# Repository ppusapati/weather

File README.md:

# Weather Station Firmware

## STM32F407 Weather Station — Embedded Rust Firmware

A production-grade weather station firmware written in Rust targeting the **STM32F407VGT6** MCU.
It collects environmental data from multiple sensors and transmits readings over
**WiFi (ATWINC1500), BLE (RN4870), LoRa, UART, MQTT, and HTTP** — with optional
Ethernet (W5500) and Cellular (SIM7600E-H) connectivity.

---

## Architecture Overview

```
┌─────────────────────────────────────────────────────────────┐
│                    APPLICATION LAYER                        │
│  ┌──────────┐ ┌────────────┐ ┌──────────┐ ┌────────────┐  │
│  │Scheduler │ │Data Pipeline│ │  Power   │ │    OTA     │  │
│  │          │ │  & Fusion  │ │  Mgmt    │ │  Updater   │  │
│  └──────────┘ └────────────┘ └──────────┘ └────────────┘  │
├─────────────────────────────────────────────────────────────┤
│                  COMMUNICATION LAYER                        │
│  ┌──────┐ ┌─────┐ ┌──────┐ ┌──────┐ ┌──────┐ ┌────────┐  │
│  │ WiFi │ │ BLE │ │ LoRa │ │ UART │ │ MQTT │ │  HTTP  │  │
│  └──────┘ └─────┘ └──────┘ └──────┘ └──────┘ └────────┘  │
├─────────────────────────────────────────────────────────────┤
│                     DRIVER LAYER                            │
│  ┌───────┐ ┌──────────┐ ┌──────┐ ┌──────┐ ┌───────────┐  │
│  │BME280 │ │Wind Speed│ │ Rain │ │  UV  │ │   Light   │  │
│  │Temp/  │ │& Dir     │ │Gauge │ │Index │ │  (BH1750) │  │
│  │Hum/Pr │ │(AS5600)  │ │(Tip) │ │SI1145│ │           │  │
│  └───────┘ └──────────┘ └──────┘ └──────┘ └───────────┘  │
├─────────────────────────────────────────────────────────────┤
│                 HARDWARE ABSTRACTION                        │
│  ┌──────┐ ┌──────┐ ┌──────┐ ┌──────┐ ┌──────┐ ┌───────┐  │
│  │ I2C  │ │ SPI  │ │ ADC  │ │ GPIO │ │ UART │ │ Timer │  │
│  └──────┘ └──────┘ └──────┘ └──────┘ └──────┘ └───────┘  │
├─────────────────────────────────────────────────────────────┤
│                   STM32F407 HARDWARE                        │
│  ARM Cortex-M4F @ 168 MHz · 192KB SRAM · 1MB Flash        │
└─────────────────────────────────────────────────────────────┘
```

## MCU Selection — STM32F407VGT6

| Criterion | STM32F407VGT6 |
|---|---|
| CPU | ARM Cortex-M4F @ 168 MHz (with FPU) |
| RAM | 192 KB SRAM (128 KB + 64 KB CCM) |
| Flash | 1 MB internal |
| WiFi | ATWINC1500 module (SPI3) |
| Bluetooth | RN4870 BLE 5.0 module (USART3) |
| ADC | 3x 12-bit SAR, 16 channels |
| I2C / SPI / UART | 3 / 3 / 4 |
| GPIO | 82 programmable |
| Standby | ~2 µA |
| Temp range | -40°C to +105°C (Industrial) |
| Rust support | `stm32f4xx-hal` + `cortex-m-rt` (mature) |

**Why STM32F407?** Industrial temperature range for outdoor deployment, hardware FPU for
sensor math, three SPI buses for concurrent LoRa/Ethernet/WiFi, dedicated UART for each
communication module, and excellent Rust embedded-hal support. Single-MCU architecture
simplifies firmware (one codebase, one toolchain).

## Sensors

| Sensor | Measures | Interface | Address / Pin |
|---|---|---|---|
| BME280 | Temperature, humidity, pressure | I2C | 0x76 |
| AS5600 | Wind direction (magnetic encoder) | I2C | 0x36 |
| Anemometer | Wind speed (pulse count) | GPIO interrupt | GPIO 4 |
| Rain gauge | Rainfall (tipping bucket) | GPIO interrupt | GPIO 5 |
| SI1145 | UV index | I2C | 0x60 |
| BH1750 | Ambient light (lux) | I2C | 0x23 |

## Communication Channels

| Channel | Protocol | Use Case |
|---|---|---|
| **WiFi** | 802.11n | Primary uplink to cloud/MQTT broker |
| **BLE 5.0** | GATT | Mobile app config & live readings |
| **LoRa** | LoRaWAN (SX1276 via SPI) | Long-range low-power telemetry |
| **UART** | Serial 115200 | Debug console & wired data export |
| **MQTT** | MQTT v3.1.1 over TCP/TLS | Cloud telemetry (over WiFi) |
| **HTTP** | REST JSON API | Local web dashboard + OTA updates |

## Industry Modules

The firmware supports optional industry-specific extensions via Cargo features:

| Feature | Industry | Additional Sensors | Analytics |
|---------|----------|-------------------|-----------|
| `agriculture` | Precision Farming | Soil moisture (×2), soil temp, leaf wetness | ET₀, GDD, frost alerts, irrigation scheduling, disease risk, spray windows |
| `solar` | Photovoltaic Monitoring | Pyranometer, panel temp (×2), power meter | Irradiance, yield estimation, peak sun hours, performance ratio, soiling loss, cloud transients |
| `india` | Indian Regional | PM2.5 particulate sensor | Monsoon tracking, IMD heat wave alerts, cyclone detection, NAQI air quality, IST timezone, IN865 LoRa |
| `all-industries` | All | All above | All above |
| `cellular` | Remote Sites | SIM7600E-H LTE modem | Cellular uplink for remote stations |
| `ethernet` | Industrial | W5500 wired Ethernet | Reliable wired connectivity + Modbus TCP |
| `sdcard` | Data Logging | Micro-SD card (SPI2) | FAT32 CSV logging with daily file rotation, GB-scale storage |
| `all-comms` | All Comms | Cellular + Ethernet + SD card | All communication + storage channels |
| `full-system` | Everything | All sensors + all comms | All analytics + SCADA + Cloud |

### Operating Modes

| Mode | Cloud (MQTT/HTTP) | SCADA (Modbus RS485) | Selection |
|------|:-----------------:|:--------------------:|-----------|
| **Cloud** | Yes | — | DIP 0:0 |
| **SCADA** | Yes | Yes | DIP 0:1 |
| **Hybrid** | Yes | Yes | DIP 1:0 (default) |

```bash
# Build with agriculture module
cargo build --release --features agriculture

# Build with solar module
cargo build --release --features solar

# Build with India regional module
cargo build --release --features india

# Build with all industry modules
cargo build --release --features all-industries

# Build with cellular modem support
cargo build --release --features cellular

# Build with Ethernet support
cargo build --release --features ethernet

# Build with SD card data logging
cargo build --release --features sdcard

# Full system: all industries + all comms
cargo build --release --features full-system
```

See [docs/INDUSTRY_AGRICULTURE.md](docs/INDUSTRY_AGRICULTURE.md),
[docs/INDUSTRY_SOLAR.md](docs/INDUSTRY_SOLAR.md),
[docs/INDUSTRY_INDIA.md](docs/INDUSTRY_INDIA.md), and
[docs/STM32_SCADA.md](docs/STM32_SCADA.md) for detailed documentation.

## Building

```bash
# Install Rust + ARM toolchain
rustup install nightly
rustup target add thumbv7em-none-eabihf
cargo install probe-rs-tools

# Build (base weather station)
cd firmware
cargo build --release --target thumbv7em-none-eabihf

# Flash via SWD (ST-Link V2)
probe-rs run --chip STM32F407VGTx target/thumbv7em-none-eabihf/release/weather-station
```

## Project Structure

```
weather/
├── README.md
├── docs/
│   ├── ARCHITECTURE.md
│   ├── REQUIREMENTS.md
│   ├── API.md
│   ├── HARDWARE.md
│   ├── INDUSTRY_INDIA.md
│   └── diagrams/
│       ├── system_architecture.md
│       ├── circuit_diagram.md
│       ├── communication_flow.md
│       ├── state_machine.md
│       ├── data_pipeline.md
│       └── sequence_diagrams.md
├── firmware/
│   ├── Cargo.toml
│   ├── build.rs
│   ├── .cargo/config.toml
│   ├── memory.x
│   └── src/
│       ├── main.rs
│       ├── config.rs
│       ├── error.rs
│       ├── drivers/
│       │   ├── mod.rs
│       │   ├── bme280.rs
│       │   ├── wind.rs
│       │   ├── rain.rs
│       │   ├── uv.rs
│       │   ├── light.rs
│       │   ├── soil_moisture.rs  (agriculture)
│       │   ├── soil_temp.rs      (agriculture/solar)
│       │   ├── leaf_wetness.rs   (agriculture)
│       │   ├── pyranometer.rs    (solar)
│       │   ├── pm25.rs           (india)
│       │   ├── stm32f407.rs     (MCU HAL + pin map)
│       │   ├── atwinc1500.rs   (WiFi SPI driver)
│       │   └── rn4870.rs       (BLE UART driver)
│       ├── comms/
│       │   ├── mod.rs
│       │   ├── wifi.rs
│       │   ├── ble.rs
│       │   ├── lora.rs
│       │   ├── uart_console.rs
│       │   ├── mqtt.rs
│       │   ├── http.rs
│       │   └── modbus_rtu.rs    (Modbus RS485 slave)
│       ├── core/
│       │   ├── mod.rs
│       │   ├── scheduler.rs
│       │   ├── data_pipeline.rs
│       │   ├── power.rs
│       │   ├── ota.rs
│       │   └── mode_manager.rs  (SCADA/Cloud/Hybrid)
│       ├── industry/
│       │   ├── mod.rs
│       │   ├── agriculture.rs    (agriculture)
│       │   ├── solar.rs          (solar)
│       │   └── india.rs          (india)
│       ├── storage/
│       │   ├── mod.rs
│       │   └── flash.rs
│       └── utils/
│           ├── mod.rs
│           ├── fmt.rs
│           ├── ring_buffer.rs
│           └── crc.rs
└── tests/
    └── integration.rs
```

## License

MIT

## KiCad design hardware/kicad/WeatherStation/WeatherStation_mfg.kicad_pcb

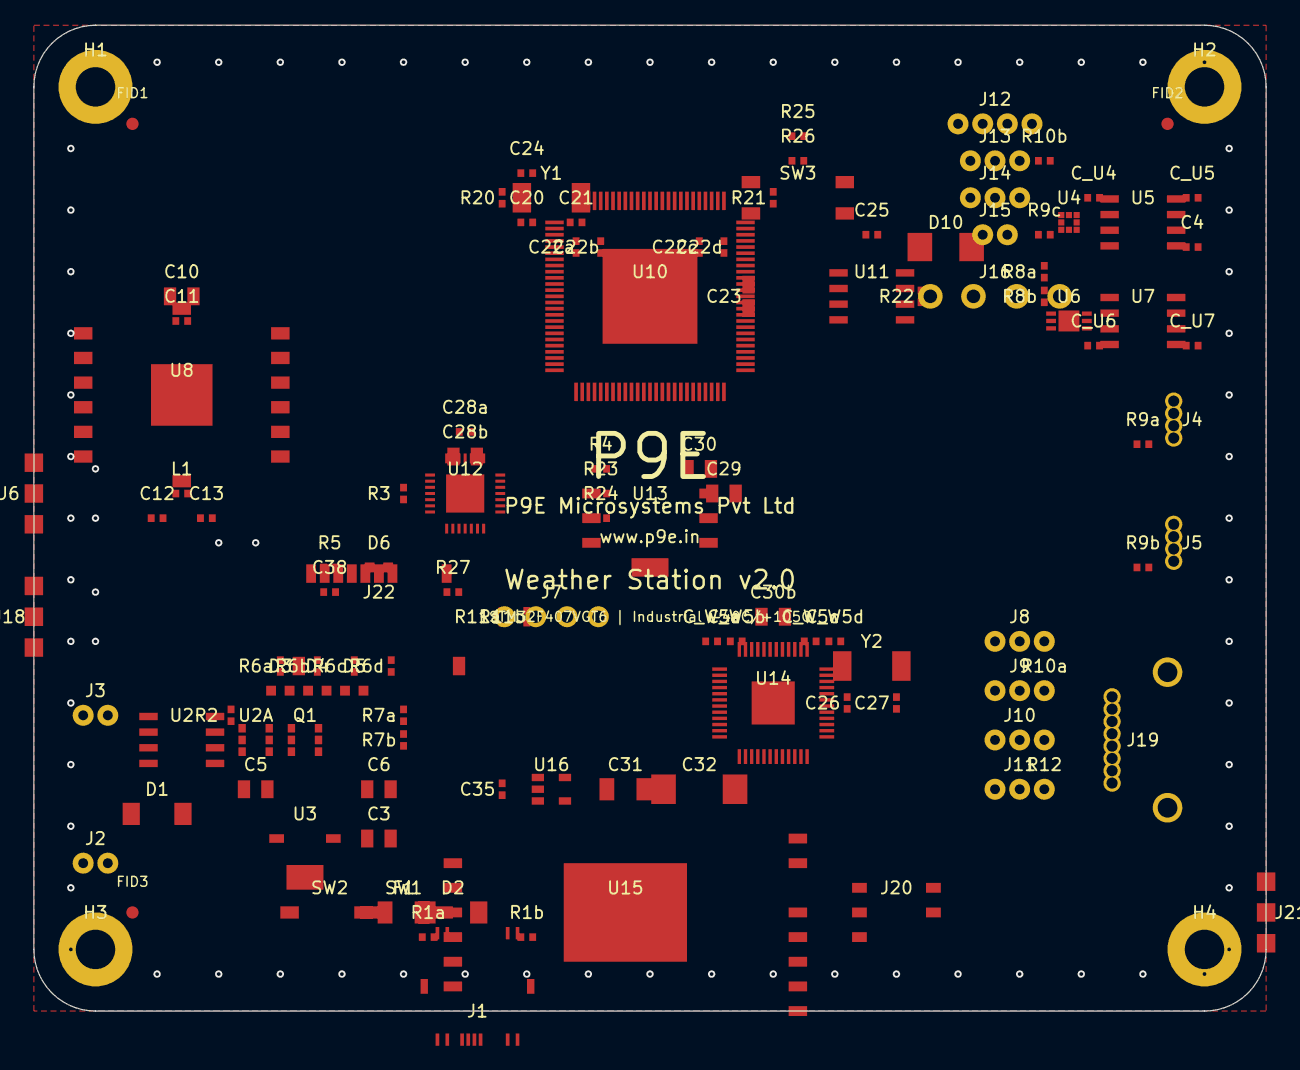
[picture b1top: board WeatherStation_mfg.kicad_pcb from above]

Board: 4 copper layers, 100.0 x 80.0 mm, 124 parts (0 on the bottom side), 76 nets, no tracks yet.

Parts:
C3: 22uF; C_0805_2012Metric
C4, C35: 1uF; C_0402_1005Metric
C5, C6, C10, C28b, C30, C30b: 10uF; C_0805_2012Metric
C11, C22a, C22b, C22c, C22d, C24, C25, C28a, C38: 100nF; C_0402_1005Metric
C12: 1.5pF; C_0402_1005Metric
C13: 3.3pF; C_0402_1005Metric
C20, C21: 20pF; C_0402_1005Metric
C23, C29: 4.7uF; C_0805_2012Metric
C26, C27: 18pF; C_0402_1005Metric
C31: 100uF; C_1206_3216Metric
C32: 470uF; CP_EIA-7343-31_Kemet-D
C_U4, C_U5, C_U6, C_U7: 100nF; C_0402_1005Metric
C_W5a, C_W5b, C_W5c, C_W5d: 100nF; C_0402_1005Metric
D1: SS14; D_SMA
D2: SMAJ5.0A; D_SMA
D3: LED_Red; LED_0603_1608Metric
D4, D6: LED_Green; LED_0603_1608Metric
D5: LED_Blue; LED_0603_1608Metric
D10: SMBJ6.0CA; D_SMB
F1: 500mA; Fuse_1206_3216Metric
FID1, FID2, FID3: Fiducial; Fiducial_1mm_Mask2mm
H1, H2, H3, H4: MountingHole_M3; MountingHole_3.2mm_M3_Pad_Via
J1: USB-C; USB_C_Receptacle_GCT_USB4105
J2: SOLAR_IN; JST_PH_B2B-PH-K_1x02_P2.00mm_Vertical
J3: BATTERY; JST_PH_B2B-PH-K_1x02_P2.00mm_Vertical
J4: ANEMOMETER; RJ11_Amphenol_54601
J5: RAIN_GAUGE; RJ11_Amphenol_54601
J6: SMA_LoRa; SMA_Amphenol_132289_EdgeMount
J7: DEBUG_UART; PinHeader_1x04_P2.54mm_Vertical
J8: SOIL_MOIST_1; JST_PH_B3B-PH-K_1x03_P2.00mm_Vertical
J9: SOIL_MOIST_2; JST_PH_B3B-PH-K_1x03_P2.00mm_Vertical
J10: SOIL_TEMP; JST_PH_B3B-PH-K_1x03_P2.00mm_Vertical
J11: LEAF_WET; JST_PH_B3B-PH-K_1x03_P2.00mm_Vertical
J12: PYRANOMETER; JST_PH_B4B-PH-K_1x04_P2.00mm_Vertical
J13: PANEL_TEMP_F; JST_PH_B3B-PH-K_1x03_P2.00mm_Vertical
J14: PANEL_TEMP_B; JST_PH_B3B-PH-K_1x03_P2.00mm_Vertical
J15: POWER_PULSE; JST_PH_B2B-PH-K_1x02_P2.00mm_Vertical
J16: RS485_Bus; PhoenixContact_MC_01x04_G_3.5mm
J18: SMA_WiFi; SMA_Amphenol_132289_EdgeMount
J19: RJ45_Magjack; RJ45_Amphenol_RJHSE-5380
J20: NanoSIM; NanoSIM_Molex_78800
J21: SMA_LTE; SMA_Amphenol_132289_EdgeMount
J22: MicroSD; MicroSD_Molex_5031821852
L1: 5.6nH; L_0402_1005Metric
Q1: FS8205A; SOT-23-6
R1a, R1b: 5.1k; R_0402_1005Metric
R2: 2.2k; R_0402_1005Metric
R3, R4, R9a, R9b, R9c, R12, R20, R21, R25, R26, R27: 10k; R_0402_1005Metric
R5: 330R; R_0402_1005Metric
R6a, R6b, R6c, R6d: 1k; R_0402_1005Metric
R7a, R7b: 100k; R_0402_1005Metric
R8a, R8b, R10a, R10b: 4.7k; R_0402_1005Metric
R11a, R11b, R23, R24: 100R; R_0402_1005Metric
R22: 120R; R_0402_1005Metric
SW1: BOOT; SW_SPST_PTS645
SW2: RESET; SW_SPST_PTS645
SW3: MODE_DIP; SW_DIP_SPSTx02_Slide_6.7x6.64mm_W8.61mm_P2.54mm
U2: TP4056; SOIC-8_3.9x4.9mm_P1.27mm
U2A: DW01A; SOT-23-6
U3: AMS1117-3.3; SOT-223-3_TabPin2
U4: BME280; Bosch_BME280_LGA-8_2.5x2.5mm
U5: AS5600; SOIC-8_3.9x4.9mm_P1.27mm
U6: SI1145; QFN-10-1EP_3x3mm_P0.6mm
U7: BH1750FVI; SOIC-8_3.9x4.9mm_P1.27mm
U8: SX1276/RFM95W; RFM95W
U10: STM32F407VGT6; LQFP-100_14x14mm_P0.5mm
U11: MAX3485ESA+; SOIC-8_3.9x4.9mm_P1.27mm
U12: ATWINC1500; QFN-28-1EP_5x5mm_P0.5mm_EP3.1x3.1mm
U13: RN4870-I/RM; RN4870_11.5x8mm
U14: W5500; LQFP-48_7x7mm_P0.5mm
U15: SIM7600E-H; SIM7600EH_LCC
U16: TPS7A2033; SOT-23-5
Y1: 8MHz; Crystal_SMD_HC49-SD
Y2: 25MHz; Crystal_SMD_HC49-SD

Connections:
+3V3: C3.1, C4.1, C10.1, C11.1, C22a.1, C22b.1, C22c.1, C22d.1, C23.1, C25.1, C28a.1, C28b.1, C29.1, C30.1, C30b.1, C35.1, C38.1, C_U4.1, C_U5.1, C_U6.1, C_U7.1, C_W5a.1, C_W5b.1, C_W5c.1, C_W5d.1, D5.2, J4.3, J5.3, J7.3, J8.1, J9.1, J10.1, J11.1, J12.1, J13.1, J14.1, J22.4, R3.1, R4.1, R6c.1, R8a.1, R8b.1, R9a.1, R9b.1, R9c.1, R10a.1, R10b.1, R20.1, R27.1, U3.2, U4.5, U4.8, U5.7, U5.8, U6.6, U7.1, U7.8, U8.14, U10.7, U10.47, U10.72, U10.99, U11.8, U12.14, U13.5, U14.12, U16.1, U16.3
ANEM_SIG: J4.1, R9a.2
BLE_RST: R4.2, U10.63, U13.3
BLE_RX: R24.1, U10.30, U13.2
BLE_STATUS: U10.64, U13.4
BLE_TX: R23.1, U10.29, U13.1
BOOT0: R21.1, SW1.1
CELL_DTR: U10.62, U15.5
CELL_PWRKEY: U10.60, U15.3
CELL_RI: U10.1, U15.6
CELL_RX: U10.79, U15.1
CELL_STATUS: U10.61, U15.4
CELL_TX: U10.78, U15.2
CHRG_STAT: D3.2, R6a.1, U2.1
ETH_CS: U10.31, U14.4
ETH_INT: U10.59, U14.6
ETH_RST: U10.58, U14.5
ETH_RXN: J19.6, U14.28
ETH_RXP: J19.3, U14.27
ETH_TXN: J19.2, U14.26
ETH_TXP: J19.1, U14.25
ETH_XTAL1: C26.1, U14.35, Y2.1
ETH_XTAL2: C27.1, U14.36, Y2.2
GND: C3.2, C4.2, C5.2, C6.2, C10.2, C11.2, C12.2, C13.2, C20.2, C21.2, C22a.2, C22b.2, C22c.2, C22d.2, C23.2, C24.2, C25.2, C26.2, C27.2, C28a.2, C28b.2, C29.2, C30.2, C30b.2, C31.2, C32.2, C35.2, C38.2, C_U4.2, C_U5.2, C_U6.2, C_U7.2, C_W5a.2, C_W5b.2, C_W5c.2, C_W5d.2, D2.2, D3.1, D4.1, D5.1, D6.1, H1.1, H2.1, H3.1, H4.1, J1.A1, J1.A12, J1.B1, J1.B12, J1.S1, J1.S2, J2.2, J3.2, J4.2, J5.2, J6.2, J6.3, J7.4, J8.2, J9.2, J10.2, J11.2, J12.2, J13.2, J14.2, J15.2, J16.3, J16.4, J18.2, J18.3, J19.S1, J19.S2, J20.C5, J21.2, J21.3, J22.3, J22.6, J22.S1, J22.S2, Q1.1, Q1.2, R1a.1, R1b.1, R2.2, R7b.2, R12.2, R21.2, R25.2, R26.2, SW1.2, SW2.2, SW3.3, SW3.4, U2.5, U2.7, U2A.2, U3.1, U4.1, U4.3, U5.3, U6.7, U6.11, U7.2, U7.3, U8.1, U8.13, U8.15, U10.48, U10.73, U10.100, U10.101, U11.5, U12.21, U12.29, U13.6, U13.7, U14.24, U14.49, U15.8, U15.GND, U16.2
HSE_IN: C20.1, U10.90, Y1.1
HSE_OUT: C21.1, U10.91, Y1.2
I2C1_SCL: R8b.2, U4.7, U5.2, U6.2, U7.6, U10.27
I2C1_SDA: R8a.2, U4.6, U5.1, U6.1, U7.4, U10.26
LEAF_WET_SIG: J11.3, R12.1
LORA_ANT: C12.1, L1.1, U8.12
LORA_CS: U8.5, U10.83
LORA_DIO0: U8.7, U10.95
LORA_RST: U8.6, U10.94
LTE_ANT: J21.1, U15.9
MODE_SW1: R25.1, SW3.1
MODE_SW2: R26.1, SW3.2
NRST: C24.1, R20.2, SW2.1, U10.93
PANEL_TEMP1_DATA: J13.3, R10b.2
POWER_PULSE: J15.1, R9c.2
RAIN_SIG: J5.1, R9b.2
RS485_A: D10.1, J16.1, R22.1, U11.6
RS485_B: D10.2, J16.2, R22.2, U11.7
RS485_DE: U11.2, U11.3
SD_CS: J22.1, U10.65
SD_DET: J22.CD, R27.2, U10.66
SIM_CLK: J20.C3, U15.12
SIM_DATA: J20.C7, U15.13
SIM_RST: J20.C2, U15.11
SIM_VCC: J20.C1, U15.10
SOIL_TEMP_DATA: J10.3, R10a.2
SPI1_MISO: U8.3, U10.25
SPI1_MOSI: U8.2, U10.23
SPI1_SCK: U8.4, U10.24
SPI2_MISO: J22.7, U10.33, U14.2
SPI2_MOSI: J22.2, U10.34, U14.3
SPI2_SCK: J22.5, U10.32, U14.1
SPI3_MISO: U10.52, U12.2
SPI3_MOSI: U10.53, U12.3
SPI3_SCK: U10.51, U12.1
STATUS_LED: D6.2, R5.1
UART1_RX: J7.2, R11b.1
UART1_TX: J7.1, R11a.1
UART2_RX: U10.82, U11.1
UART2_TX: U10.81, U11.4
USB_DM: J1.A7, U10.88
USB_DP: J1.A6, U10.87
VBAT: C6.1, J3.1, Q1.5, Q1.6, R7a.1, U2.4, U2A.5, U2A.6, U3.3
VBAT_SENSE: R7a.2, R7b.1
VBAT_SIM: C31.1, C32.1, U15.7, U16.5
VBUS_5V: C5.1, D1.2, D2.1, F1.1, F1.2, J1.A4, J1.A9, J1.B4, J1.B9, U2.3
VSOLAR: D1.1, J2.1
WIFI_ANT: J18.1, U12.28
WIFI_CS: U10.3, U12.4
WIFI_EN: R3.2, U10.2, U10.6, U12.7
WIFI_IRQ: U10.5, U12.6
WIFI_RST: U10.4, U12.5

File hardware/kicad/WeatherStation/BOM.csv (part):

Reference,Value,Footprint,Qty,Description,Manufacturer,MPN,Supplier,Notes
U12,ATWINC1500-MR210PB,Package_DFN_QFN:QFN-28_5x5mm,1,"WiFi 802.11 b/g/n Module, SPI, Integrated TCP/IP, -40/+85C",Microchip,ATWINC1500-MR210PB,Mouser,"SPI3 (PB3-PB5), CS=PE3, RST=PE4, IRQ=PE5, CHIP_EN=PE6"
U13,RN4870-I/RM,Module:RN4870,1,"BLE 5.0 Module, UART, Integrated GATT, -40/+85C",Microchip,RN4870-I/RM130,Mouser,"USART3 (PB10/PB11), RST=PD8, STATUS=PD9, On-module antenna"
U14,W5500,Package_QFP:LQFP-48_7x7mm_P0.5mm,1,"Hardwired TCP/IP Ethernet Controller, SPI, 8 sockets, -40/+85C",WIZnet,W5500,Mouser,"SPI2 (PB12-PB15), RST=PD3, INT=PD4, 25MHz crystal"
U15,SIM7600E-H,Module:SIM7600,1,"LTE Cat-4 Cellular Module, UART, 150Mbps DL, -40/+85C",SIMCom,SIM7600E-H,Mouser,"UART4 (PC10/PC11), PWRKEY=PD5, STATUS=PD6, DTR=PD7, RI=PE2"
U16,TPS7A2033DGNR,Package_TO_SOT_SMD:SOT-23-5,1,"3.3V to 3.8V LDO for SIM7600, 2A max",Texas Instruments,TPS7A2033DGNR,Mouser,"3.8V output for SIM7600 VBAT, 2A peak current capable"
U2,TP4056,Package_SO:SOIC-8_3.9x4.9mm_P1.27mm,1,"LiPo Battery Charger IC, 500mA",Nanjing Top Power,TP4056,LCSC,"Set RPROG=2.2k for 500mA charge current"
U2A,DW01A,Package_SO:SOT-23-6,1,"Battery Protection IC (OVP/UVP/OCP)",Fortune Semi,DW01A-G,LCSC,"Paired with FS8205A dual MOSFET"
Q1,FS8205A,Package_SO:SOT-23-6,1,"Dual N-MOSFET for battery protection",Fortune Semi,FS8205A,LCSC,"Use with DW01A for Li-ion protection"
U3,AMS1117-3.3,Package_TO_SOT_SMD:SOT-223-3_TabPin2,1,"3.3V LDO Regulator, 1A, LDO",AMS,AMS1117-3.3,LCSC,"Dropout 1.1V typical. Input cap 10uF, output 22uF"
U4,BME280,Package_LGA:Bosch_BME280_LGA-8_2.5x2.5mm,1,"Temp/Humidity/Pressure Sensor, I2C 0x76",Bosch Sensortec,BME280,Mouser,"Accuracy: +/-1C, +/-3%RH, +/-1hPa"
U5,AS5600,Package_SO:SOIC-8_3.9x4.9mm_P1.27mm,1,"12-bit Magnetic Rotary Encoder, I2C 0x36",ams-OSRAM,AS5600-ASOM,Mouser,"Requires diametrically magnetized magnet on vane shaft"
U6,SI1145,Package_DFN_QFN:QFN-10-1EP_3x3mm_P0.6mm,1,"UV Index / IR / Visible Light Sensor, I2C 0x60",Silicon Labs,SI1145-A10-GMR,DigiKey,"Digital output, built-in ADC"
U7,BH1750FVI,Package_SO:SOIC-8_3.9x4.9mm_P1.27mm,1,"Ambient Light Sensor, I2C 0x23, 1-65535 lux",ROHM,BH1750FVI-TR,Mouser,"16-bit digital output, auto-ranging"
U8,SX1276,Module:RFM95W,1,"LoRa Transceiver Module 868/915MHz, SPI",Semtech/HopeRF,RFM95W-868S2,Mouser,"SX1276 based, +20dBm TX, -148dBm RX sensitivity"
J1,USB-C,Connector_USB:USB_C_Receptacle_GCT_USB4105,1,"USB Type-C Receptacle, 16-pin",GCT,USB4105-GF-A,DigiKey,"CC1/CC2 with 5.1k pulldown for UFP/sink"
J2,JST_PH_2P,Connector_JST:JST_PH_B2B-PH-K_1x02_P2.00mm_Vertical,1,"Solar Panel Input, 6V max",JST,B2B-PH-K-S,,"Polarity: Pin1=V+, Pin2=GND"
J3,JST_PH_2P,Connector_JST:JST_PH_B2B-PH-K_1x02_P2.00mm_Vertical,1,"18650 LiPo Battery Connector",JST,B2B-PH-K-S,,"Polarity: Pin1=V+, Pin2=GND. Use protected cell."
J4,RJ11_4P4C,Connector_RJ:RJ11_Amphenol_54601,1,"Anemometer Connector (wind speed)",Amphenol,54601-908LF,,"Reed switch type, 2 active pins"
J5,RJ11_4P4C,Connector_RJ:RJ11_Amphenol_54601,1,"Rain Gauge Connector (tipping bucket)",Amphenol,54601-908LF,,"Reed switch type, 2 active pins"
J6,SMA_Edge,Connector_Coaxial:SMA_Amphenol_132289_EdgeMount,1,"LoRa Antenna SMA Female, 50ohm",Amphenol,132289,Mouser,"Edge mount, maintain 50ohm trace to U8"
J7,Header_1x04,Connector_PinHeader_2.54mm:PinHeader_1x04_P2.54mm_Vertical,1,"UART Debug Header (TX/RX/3V3/GND)",Generic,,,"Pin1=TX, Pin2=RX, Pin3=3V3, Pin4=GND"
J8,JST_PH_3P,Connector_JST:JST_PH_B3B-PH-K_1x03_P2.00mm_Vertical,1,"Soil Moisture Sensor (shallow) — Agriculture",JST,B3B-PH-K-S,,"V+/GND/SIG, Capacitive type"
J9,JST_PH_3P,Connector_JST:JST_PH_B3B-PH-K_1x03_P2.00mm_Vertical,1,"Soil Moisture Sensor (deep) — Agriculture",JST,B3B-PH-K-S,,"V+/GND/SIG, Capacitive type"
J10,JST_PH_3P,Connector_JST:JST_PH_B3B-PH-K_1x03_P2.00mm_Vertical,1,"Soil Temperature DS18B20 — Agriculture",JST,B3B-PH-K-S,,"V+/GND/DATA, Waterproof probe"
J11,JST_PH_3P,Connector_JST:JST_PH_B3B-PH-K_1x03_P2.00mm_Vertical,1,"Leaf Wetness Sensor — Agriculture",JST,B3B-PH-K-S,,"V+/GND/SIG, Resistive type"
J12,JST_PH_4P,Connector_JST:JST_PH_B4B-PH-K_1x04_P2.00mm_Vertical,1,"Pyranometer ML8511 — Solar",JST,B4B-PH-K-S,,"V+/GND/OUT/EN, Shares GPIO7 with J8"
J13,JST_PH_3P,Connector_JST:JST_PH_B3B-PH-K_1x03_P2.00mm_Vertical,1,"Panel Temp Front DS18B20 — Solar",JST,B3B-PH-K-S,,"V+/GND/DATA, Epoxy-mount to panel front"
J14,JST_PH_3P,Connector_JST:JST_PH_B3B-PH-K_1x03_P2.00mm_Vertical,1,"Panel Temp Back DS18B20 — Solar",JST,B3B-PH-K-S,,"V+/GND/DATA on GPIO19"
J15,JST_PH_2P,Connector_JST:JST_PH_B2B-PH-K_1x02_P2.00mm_Vertical,1,"Power Meter Pulse Input — Solar",JST,B2B-PH-K-S,,"SIG/GND, S0 pulse interface"
D1,SS14,Diode_SMD:D_SMA,1,"Schottky Diode, 40V 1A — Solar input protection",Vishay,SS14-E3/61T,,"Low Vf for solar efficiency"
D2,SMAJ5.0A,Diode_SMD:D_SMA,1,"TVS Diode, 5V — USB ESD protection",Littelfuse,SMAJ5.0A,,"Bidirectional preferred for USB"
D3,LED_Red,LED_SMD:LED_0603_1608Metric,1,"Charging Indicator LED",Generic,,,"With 1k series resistor"
D4,LED_Green,LED_SMD:LED_0603_1608Metric,1,"Charge Complete / Standby LED",Generic,,,"With 1k series resistor"
D5,LED_Blue,LED_SMD:LED_0603_1608Metric,1,"Power On Indicator, 3V3 rail",Generic,,,"With 1k series resistor"
D6,LED_Green,LED_SMD:LED_0603_1608Metric,1,"Status LED on GPIO2",Generic,,,"With 330R series resistor"
R1,5.1k,Resistor_SMD:R_0402_1005Metric,2,"USB-C CC1/CC2 pulldown (UFP)",Generic,,"LCSC","0402, 1%, 0.1W"
R2,2.2k,Resistor_SMD:R_0402_1005Metric,1,"TP4056 RPROG — sets 500mA charge",Generic,,"LCSC","0402, 1%, 0.1W"
R3,10k,Resistor_SMD:R_0402_1005Metric,1,"ATWINC1500 CHIP_EN pull-up",Generic,,"LCSC","0402, 5%, 0.1W"
R4,10k,Resistor_SMD:R_0402_1005Metric,1,"RN4870 RST pull-up",Generic,,"LCSC","0402, 5%, 0.1W"
R5,330,Resistor_SMD:R_0402_1005Metric,1,"Status LED current limiter (GPIO2)",Generic,,"LCSC","0402, 5%, 0.1W"
R6,1k,Resistor_SMD:R_0402_1005Metric,4,"LED series resistors (D3-D5 + spare)",Generic,,"LCSC","0402, 5%, 0.1W"
R7,100k,Resistor_SMD:R_0402_1005Metric,2,"Battery voltage divider (100k/100k)",Generic,,"LCSC","0402, 1%, 0.1W"
R8,4.7k,Resistor_SMD:R_0402_1005Metric,2,"I2C SDA/SCL pull-up resistors",Generic,,"LCSC","0402, 5%, 0.1W"
R9,10k,Resistor_SMD:R_0402_1005Metric,3,"GPIO pull-ups (wind/rain/power pulse)",Generic,,"LCSC","0402, 5%, 0.1W"
R10,4.7k,Resistor_SMD:R_0402_1005Metric,2,"1-Wire pull-ups (soil temp + panel temp)",Generic,,"LCSC","0402, 5%, 0.1W"
R11,100,Resistor_SMD:R_0402_1005Metric,2,"UART TX/RX series protection",Generic,,"LCSC","0402, 5%, 0.1W"
R12,10k,Resistor_SMD:R_0402_1005Metric,1,"Leaf wetness pull-down",Generic,,"LCSC","0402, 5%, 0.1W"
C1,10uF,Capacitor_SMD:C_0805_2012Metric,2,"ATWINC1500 3V3 decoupling + AMS1117 input",Generic,,"LCSC","0805, 16V, X5R"
C2,100nF,Capacitor_SMD:C_0402_1005Metric,14,"IC decoupling caps (ATWINC1500 x2 + RN4870 x1 + W5500 x4 + sensors x4 + misc x3)",Generic,,"LCSC","0402, 16V, X7R"
C3,22uF,Capacitor_SMD:C_0805_2012Metric,1,"AMS1117 output cap",Generic,,"LCSC","0805, 10V, X5R"
C4,1uF,Capacitor_SMD:C_0402_1005Metric,2,"AS5600 decoupling + spare",Generic,,"LCSC","0402, 16V, X7R"
C5,10uF,Capacitor_SMD:C_0805_2012Metric,1,"TP4056 input cap",Generic,,"LCSC","0805, 16V, X5R"
SW1,BOOT,Button_SMD:SW_SPST_PTS645,1,"Boot button (GPIO0 to GND)",C&K,PTS645SM43SMTR92LFS,,"Tactile, 6mm"
SW2,RESET,Button_SMD:SW_SPST_PTS645,1,"Reset button (EN to GND)",C&K,PTS645SM43SMTR92LFS,,"Tactile, 6mm"
F1,500mA,Fuse_SMD:Fuse_1206_3216Metric,1,"Polyfuse / Resettable fuse, USB input",Bourns,MF-MSMF050-2,,"Holds 500mA, trips 1A"
H1-H4,MountingHole_M3,MountingHole:MountingHole_3.2mm_M3_Pad_Via,4,"M3 mounting holes at corners",,,,"Use M3 brass standoffs, 8mm"
FID1-FID3,Fiducial,Fiducial:Fiducial_1mm_Mask2mm,3,"PCB fiducial marks for P&P alignment",,,,
U10,STM32F407VGT6,Package_QFP:LQFP-100_14x14mm_P0.5mm,1,"ARM Cortex-M4F MCU, 168MHz, 1MB Flash, 192KB SRAM, Industrial -40/+105C",ST Microelectronics,STM32F407VGT6,Mouser/DigiKey,"Industrial temp range, FPU, 3x ADC, 6x USART"
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
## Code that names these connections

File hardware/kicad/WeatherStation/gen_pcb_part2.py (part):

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# Key pin-to-net assignments for STM32F407VGT6:
stm32_pin_nets = {
    # Left side (pins 1-25): PE2-PE6, PB3-PB5, etc.
    1: (59, "CELL_RI"),       # PE2
    2: (36, "WIFI_EN"),       # PE3 -> WIFI_CS actually. Let me fix.
    # Actually PE3=WIFI_CS, PE4=WIFI_RST, PE5=WIFI_IRQ, PE6=WIFI_EN
    3: (33, "WIFI_CS"),       # PE3
    4: (34, "WIFI_RST"),      # PE4
    5: (35, "WIFI_IRQ"),      # PE5
    6: (36, "WIFI_EN"),       # PE6
    7: (2, "+3V3"),           # VBAT
    23: (10, "SPI1_MOSI"),    # PA7 (SPI1_MOSI)
    24: (12, "SPI1_SCK"),     # PA5 (SPI1_SCK)
    25: (11, "SPI1_MISO"),    # PA6 (SPI1_MISO)

    # Bottom side (pins 26-50)
    26: (40, "I2C1_SDA"),     # PB7 (I2C1_SDA)
    27: (41, "I2C1_SCL"),     # PB6 (I2C1_SCL)
    29: (50, "BLE_TX"),       # PB10 (USART3_TX)
    30: (51, "BLE_RX"),       # PB11 (USART3_RX)
    31: (23, "ETH_CS"),       # PB12 (SPI2_NSS)
    32: (22, "SPI2_SCK"),     # PB13 (SPI2_SCK)
    33: (21, "SPI2_MISO"),    # PB14 (SPI2_MISO)
    34: (20, "SPI2_MOSI"),    # PB15 (SPI2_MOSI)
    47: (2, "+3V3"),          # VDD
    48: (1, "GND"),           # VSS

    # Right side (pins 51-75)
    51: (32, "SPI3_SCK"),     # PB3 (SPI3_SCK)
    52: (31, "SPI3_MISO"),    # PB4 (SPI3_MISO)
    53: (30, "SPI3_MOSI"),    # PB5 (SPI3_MOSI)
    58: (24, "ETH_RST"),      # PD3
    59: (25, "ETH_INT"),      # PD4
    60: (56, "CELL_PWRKEY"),  # PD5
    61: (57, "CELL_STATUS"),  # PD6
    62: (58, "CELL_DTR"),     # PD7
    63: (52, "BLE_RST"),      # PD8
    64: (53, "BLE_STATUS"),   # PD9
    65: (26, "SD_CS"),        # PD10
    66: (27, "SD_DET"),       # PD11
    72: (2, "+3V3"),          # VDD
    73: (1, "GND"),           # VSS

    # Top side (pins 76-100)
    78: (54, "CELL_TX"),      # PC10 (UART4_TX)
    79: (55, "CELL_RX"),      # PC11 (UART4_RX)
    81: (44, "UART2_TX"),     # PA2 (USART2_TX for RS485)
    82: (45, "UART2_RX"),     # PA3 (USART2_RX for RS485)
    83: (13, "LORA_CS"),      # PA4 (SPI1_NSS)
    87: (80, "USB_DP"),       # PA11 (USB_DP)
    88: (81, "USB_DM"),       # PA12 (USB_DM)
    90: (75, "HSE_IN"),       # PH0/OSC_IN
    91: (76, "HSE_OUT"),      # PH1/OSC_OUT
    93: (77, "NRST"),         # NRST
    94: (14, "LORA_RST"),     # PC4
    95: (15, "LORA_DIO0"),    # PC5
    99: (2, "+3V3"),          # VDD
    100: (1, "GND"),          # VSS
}
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
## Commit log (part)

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2026-02-26 Add initial README with project title
2026-02-27 Add ESP32-S3 weather station firmware in Rust with full documentation
    Complete weather station firmware implementation targeting the ESP32-S3 MCU:
    Documentation:
    - README with architecture overview, MCU selection rationale, build instructions
    - ARCHITECTURE.md: layered system design, dual-core task allocation, data flow
    - REQUIREMENTS.md: functional and non-functional requirements specification
    - API.md: MQTT topics, HTTP REST endpoints, BLE GATT profile, UART commands, LoRa packet format
2026-02-27 Improve code quality and add missing documentation
    - Extract duplicated HeaplessWriter to shared utils/fmt.rs with format_heapless! macro
    - Replace all silent `let _ = Result` patterns with explicit error logging
    - Add SAFETY docs for unsafe blocks in main.rs
    - Replace 20+ magic numbers with named constants in config.rs
    - Fix unwrap() to unwrap_or_default() in RuntimeConfig for robustness
    - Align power consumption figures between ARCHITECTURE.md and HARDWARE.md
2026-02-27 Add industry sensor drivers and feature flags for Agriculture and Solar
    - Add Cargo feature flags: agriculture, solar, all-industries
    - Add config constants for agriculture (soil, GDD, frost, ET, irrigation)
    - Add config constants for solar (irradiance, panel temp, yield, soiling)
    - Add soil moisture driver (capacitive ADC, dual-depth probes)
    - Add DS18B20 soil/panel temperature driver (1-Wire protocol)
    - Add leaf wetness sensor driver (resistive, with duration tracking)
2026-02-27 Add Agriculture and Solar industry modules with analytics engines
    Agriculture (--features agriculture):
    - Sensor drivers: capacitive soil moisture (dual-depth), DS18B20 soil
    temp, leaf wetness with duration tracking
    - FAO Penman-Monteith ET₀ with Hargreaves-Samani fallback
    - Growing Degree Days with configurable crop base temperatures
    - Multi-level frost alerts with humidity-adjusted radiative frost model
2026-02-27 Fix code quality issues: precision, safety, and performance
    - Fix heat index calculation to use f64 intermediates for polynomial precision
    - Add division-by-zero guards in dew point (Magnus) and ET₀ (Penman-Monteith)
    - Add wind direction NaN/Inf guard before EMA filter processing
    - Fix wind chill boundary condition (v < 5.0 instead of v <= 4.8)
    - Add alert deduplication for solar (overheat, PR, soiling) and agriculture
    (irrigation, disease) to prevent MQTT flooding
2026-02-28 Add KiCad hardware design: schematics, PCB layout, and BOM
    KiCad 7 project with hierarchical schematic design:
    - Top-level: ESP32-S3-WROOM-1-N16R8I with decoupling, boot/reset
    buttons, status LED, and GPIO pin map
    - Power supply: USB-C + solar input, TP4056 LiPo charger with
    DW01A protection, AMS1117-3.3 LDO, battery voltage divider
    - Sensors: I2C bus (BME280, AS5600, SI1145, BH1750) with pull-ups
2026-02-28 Update KiCad schematic with detailed sensor interface design
    Expanded the top-level schematic with comprehensive sensor interfaces
    including I2C, SPI, UART, and ADC connections for the ESP32-S3 weather
    station. Added hierarchical design structure with proper pin assignments.
    https://claude.ai/code/session_01XHnfZQ5BbxTCTBMCteQyVe
2026-02-28 Add comprehensive cost estimate for weather station build
    Covers all cost categories: electronic BOM ($145-191), PCB fabrication &
    assembly ($42/board), testing & calibration ($55-97/unit), outdoor station
    enclosure & mounting ($198), and packaging/shipping ($43). Includes volume
    pricing estimates and cost optimization opportunities.
    https://claude.ai/code/session_01XHnfZQ5BbxTCTBMCteQyVe
2026-02-28 Add India development report with milestones, costings, and market analysis
    Comprehensive project report covering:
    - 10-phase development timeline (~50 weeks, M1-M10)
    - Per-unit hardware costing in INR (base ₹40K, full build ₹49.5K)
    - Volume pricing from 1 to 1000 units (₹49.5K → ₹21.8K)
    - Infrastructure & equipment: lab setup (₹5.7L), cloud (₹78K/yr)
    - Human resources: 5.5 FTE team, 12 months (₹49.7L)
2026-03-13 Upgrade to industrial-grade components and harden code quality
    - PM2.5 driver: rewrite with GP2Y1014AU0F support, LED pulse timing
    (320µs/280µs), multi-sample averaging with trimmed-mean outlier
    rejection, warm-up enforcement (10s), NaN/infinity guards,
    consecutive out-of-range fault detection, EMA filtering, and
    runtime calibration API
    - india.rs: add input sanitization (is_finite guards on all sensor
2026-03-15 Add STM32F407 MCU support with SCADA/Cloud/Hybrid operating modes
    Dual-MCU architecture: STM32F407VGT6 handles sensor acquisition and
    Modbus RS485 SCADA, ESP32-S3 handles cloud connectivity (MQTT/HTTP).
    New firmware modules:
    - drivers/stm32f407.rs: MCU HAL with pin assignments, clock config,
    Modbus RS485 params, OperatingMode enum (Cloud/SCADA/Hybrid),
    DIP switch mode selection, ESP32 bridge protocol definition
2026-03-15 Migrate to single-MCU architecture: STM32F407 with external connectivity modules
    Remove ESP32-S3 dual-MCU design. STM32F407VGT6 is now the sole MCU with:
    - ATWINC1500 WiFi (SPI3), RN4870 BLE (USART3), W5500 Ethernet (SPI2),
    SIM7600E-H cellular (UART4) as external connectivity modules.
    - Updated Cargo.toml for stm32f4xx-hal, cortex-m-rt, embedded-alloc
    - New memory.x for STM32F407 (1MB Flash, 128KB RAM, 64KB CCM)
    - New drivers: atwinc1500.rs, w5500.rs, sim7600.rs, rn4870.rs
2026-03-15 Add cellular and ethernet communication channels
    - comms/cellular.rs: CellularChannel via SIM7600E-H modem (feature-gated)
    - comms/ethernet.rs: EthernetChannel via W5500 with Modbus TCP gateway (feature-gated)
    - comms/mod.rs: Add new module declarations
    https://claude.ai/code/session_01XHnfZQ5BbxTCTBMCteQyVe
2026-03-15 Update SIM7600E-H driver with full AT command engine and power sequencing
    Expanded driver with proper SignalQuality struct (RSSI, BER, RSRP, RSRQ),
    RegistrationStatus enum, CellularInfo tracking, TCP socket management,
    URC processing, and AT command helpers with timeout handling.
    https://claude.ai/code/session_01XHnfZQ5BbxTCTBMCteQyVe
2026-03-15 feat: complete single-MCU migration — remove ESP32-S3, add ATWINC1500/RN4870/W5500/SIM7600
    Migrate from dual-MCU (ESP32-S3 + STM32F407) to single-MCU (STM32F407VGT6 only)
    with external communication modules:
    Firmware changes:
    - Rewrite wifi.rs for ATWINC1500 SPI driver, ble.rs for RN4870 UART driver
    - Remove all #[cfg(feature = "stm32")] gates — STM32 is now the only target
    - Remove bridge protocol (BridgeSync task, USART3 bridge)
2026-03-15 feat: add SD card storage on SPI2 shared bus (sdcard feature)
    Add micro-SD card data logging with FAT32 CSV format and daily file
    rotation. The SD card shares SPI2 with W5500 Ethernet, using
    CriticalSectionDevice for bus arbitration (CS=PD10, detect=PD11).
    New files:
    - drivers/sdcard.rs: SPI SD card driver wrapper (embedded-sdmmc)
    - storage/sdcard.rs: FAT32 CSV logger with 512-byte sector buffer
2026-03-19 fix: remove invalid ;; comments from KiCad schematics and add SD card circuit
    KiCad's S-expression parser does not support semicolon comments.
    All ;; comment lines have been stripped from the 5 .kicad_sch files
    and WeatherStation.kicad_sym to fix "Expecting '('" parse errors.
    Also adds the SD card circuit to communication.kicad_sch:
    - J22 MicroSD_SPI holder with SPI2 bus connections
    - C38 100nF VCC decoupling capacitor
2026-03-20 feat: add ATWINC1500, RN4870, W5500, SIM7600 to communication schematic
    Add all 4 industrial communication module circuits to communication.kicad_sch:
    - U12 ATWINC1500 WiFi (SPI3): QFN-28, J18 SMA antenna, C28/C29 decoupling
    - U13 RN4870 BLE (USART3): UART module, C30/C31 decoupling
    - U14 W5500 Ethernet (SPI2): LQFP-48, Y2 25MHz crystal + C32/C33 load caps,
    J19 RJ45 Magjack, C26/C34 decoupling
    - U15 SIM7600E-H Cellular (UART4): LTE Cat-4, U16 TPS7A2033 3.8V LDO,
2026-03-20 feat: add manufacturing-ready PCB layout with 80+ component footprints
    Generate WeatherStation_mfg.kicad_pcb with complete component placement:
    MCU & Control:
    - U10 STM32F407VGT6 (LQFP-100) with 100 pads, all net assignments
    - Y1 8MHz crystal + C20/C21 load caps + 4x decoupling caps
    - U11 MAX3485 RS485 + J16 Phoenix terminal + D10 TVS
    Communication Modules:
2026-03-20 fix: add 3 missing BOM components to manufacturing PCB
    Add U2A (DW01A battery protection IC), Q1 (FS8205A dual N-MOSFET
    for battery protection), and C4 (1uF AS5600 decoupling cap) that
    were missing from the PCB layout. All BOM components now have
    corresponding footprints in the manufacturing PCB.
    https://claude.ai/code/session_01XHnfZQ5BbxTCTBMCteQyVe
2026-03-20 fix: correct connector pin counts, capacitor size, and add R6d
    Fixes from detailed BOM cross-reference audit:
    - J12 (Pyranometer): Changed from 3-pin to 4-pin JST (B4B-PH-K)
    per BOM spec (V+/GND/OUT/EN)
    - J15 (Power Pulse): Changed from 3-pin to 2-pin JST (B2B-PH-K)
    per BOM spec (SIG/GND, S0 pulse interface)
    - C30 (W5500 bulk decoupling): Fixed from 0402/100nF to 0805/10uF
2026-03-20 style: apply P9E 3-line label format on front and back silkscreen
    Front silkscreen (F.SilkS) — 3-line P9E label block:
    Line 1: P9E (3.5mm bold, company mark)
    Line 2: P9E Microsystems Pvt Ltd (1.2mm bold, full name)
    Line 3: www.p9e.in (1.0mm, website)
    Product info kept separate below the label block:
    Weather Station v2.0 | STM32F407VGT6 | Industrial -40C/+105C
2026-03-20 fix: remove ;; comments from kicad_pcb files (invalid S-expression syntax)
    KiCad PCB files use S-expression format which does not support ;; comments.
    The comment lines caused a parse error at line 102 when opening in KiCad.
    Removed all standalone comment lines from both PCB files.
    https://claude.ai/code/session_01XHnfZQ5BbxTCTBMCteQyVe
2026-03-20 fix: remove ;; comments from communication.kicad_sch (KiCad parse error)
    Same issue as the PCB files — KiCad S-expression format does not support
    ;; comments. Removed 46 comment lines causing parse error at line 2022.
    https://claude.ai/code/session_01XHnfZQ5BbxTCTBMCteQyVe
2026-03-20 fix: correct net_label→label and comma in coordinates for KiCad
    - communication.kicad_sch: replaced 12 instances of invalid `net_label`
    keyword with `label` (valid KiCad schematic syntax)
    - WeatherStation_mfg.kicad_pcb: fixed `(at 22, 58)` → `(at 22 58)`,
    commas are not valid separators in S-expressions
    https://claude.ai/code/session_01XHnfZQ5BbxTCTBMCteQyVe
2026-04-19 Fix 1: sensors.kicad_sch — add BME280 CSB→VCC, SDO→GND; AS5600 DIR→GND, OUT/PGO no-connect; BH1750 ADDR→GND
    Agent-Logs-Url: https://github.com/ppusapati/weather/sessions/bf78e071-0670-4802-a032-1f4282b37237
2026-04-19 Fix 2: WeatherStation.kicad_sch — remove ESP32-S3, add STM32F407 sub-sheet, fix title/pin annotations
    Agent-Logs-Url: https://github.com/ppusapati/weather/sessions/bf78e071-0670-4802-a032-1f4282b37237
2026-04-19 Fix 3: stm32_scada.kicad_sch — remove ESP32 bridge J17/R23/R24, remove ESP32_BRIDGE labels, update DESIGN NOTES
    Agent-Logs-Url: https://github.com/ppusapati/weather/sessions/bf78e071-0670-4802-a032-1f4282b37237
2026-04-19 Fix 4: power_supply.kicad_sch — fix AMS1117 cap note, add VBAT cap, fix battery label, update power budget
    Agent-Logs-Url: https://github.com/ppusapati/weather/sessions/bf78e071-0670-4802-a032-1f4282b37237
2026-04-19 Fix 5: circuit_diagram.md — add I2C pin connection table, update power supply decoupling notes
    Agent-Logs-Url: https://github.com/ppusapati/weather/sessions/bf78e071-0670-4802-a032-1f4282b37237
